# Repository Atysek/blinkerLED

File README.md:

# BlinkerLED
Simple board with few blinking LEDs. The board creates a LED blinking effect, making it perfect for beginners who want to learn the basics of electronics, soldering, and PCB assembly. It is easy to make and can be used as cool decoration for your room.

# PCB & Schematic
The PCB was designed in KiCad.

# BOM – Bill of Materials
| Quantity |	Name |
|----------|-------|
| 1×  | NE555P IC TIMER |
| 1×	| IC SOCKET |
| 10× | LEDs |
| 2×	| Resistors |
| 2×	| Capacitors |
| 1×	| Potentiometer |
| 2×	| Power Connectors |
| 1×	| Custom PCB	Designed in KiCAD |

# REPOSITORIES:
PCB-Pcb design and other files
GERBER-Gerber files for production
PHOTO-Photos

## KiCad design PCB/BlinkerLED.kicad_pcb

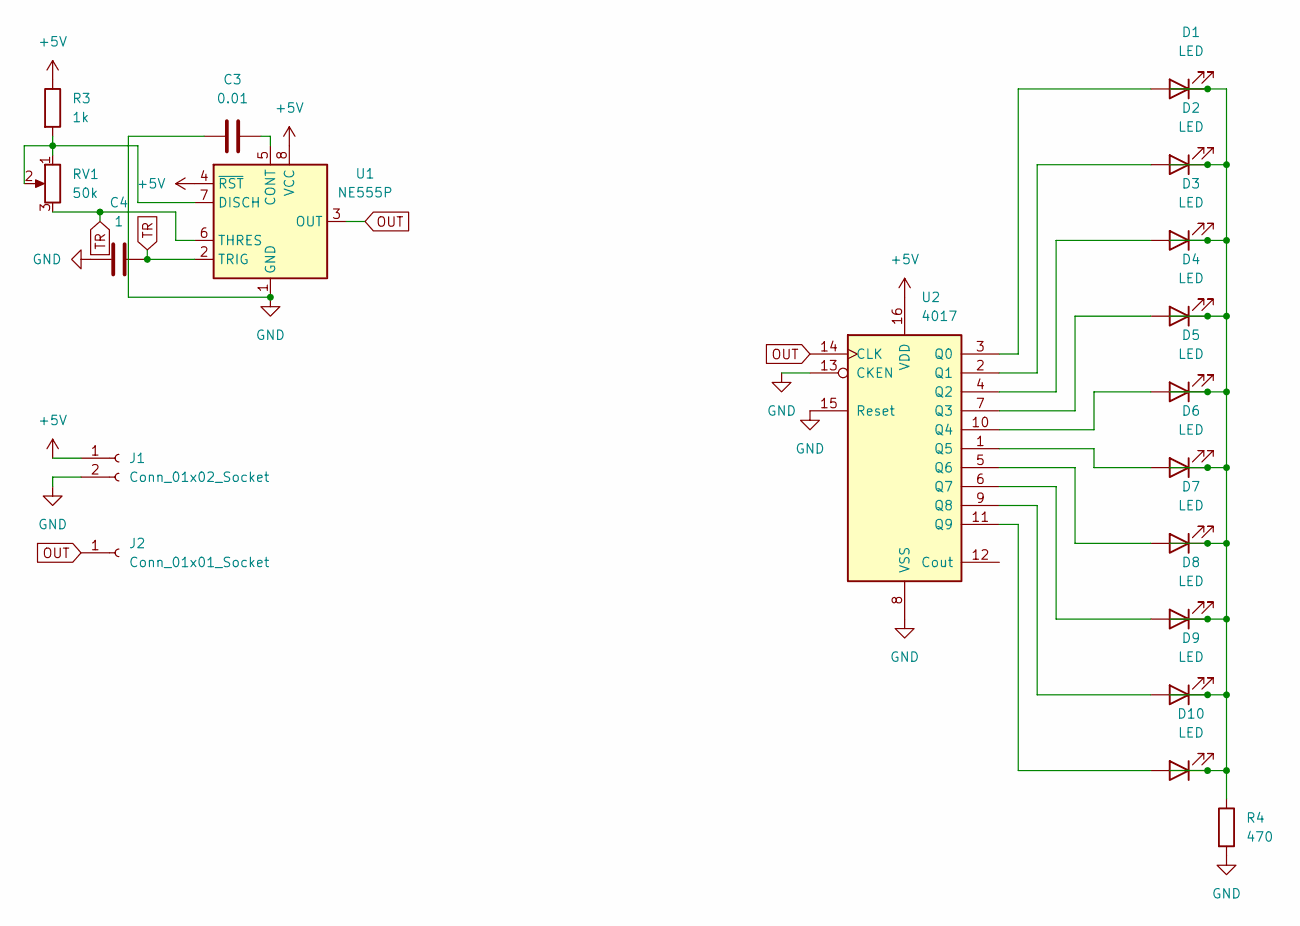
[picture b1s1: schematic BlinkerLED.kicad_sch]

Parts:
C3: 0.01; C_Disc_D7.5mm_W2.5mm_P5.00mm
C4: 1; CP_Radial_D5.0mm_P2.00mm
D1, D2, D3, D4, D5, D6, D7, D8, D9, D10: LED; LED_D3.0mm
J1: Conn_01x02_Socket; PinHeader_1x02_P2.54mm_Vertical
J2: Conn_01x01_Socket; PinHeader_1x01_P2.54mm_Vertical
R3: 1k; R_Axial_DIN0207_L6.3mm_D2.5mm_P7.62mm_Horizontal
R4: 470; R_Axial_DIN0207_L6.3mm_D2.5mm_P7.62mm_Horizontal
RV1: 50k; Potentiometer_Vishay_T93YA_Vertical
U1: NE555P; DIP-8_W7.62mm
U2: 4017; N16

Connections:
+5V: J1.1, R3.1, U1.4 (~RST), U1.8 (VCC), U2.16 (VDD)
GND: C3.1, C4.1, J1.2, R4.2, U1.1 (GND), U2.8 (VSS), U2.13 (CKEN), U2.15 (Reset)
unnamed: D1.2 (A), U2.3 (Q0)
unnamed: D1.1 (K), D2.1 (K), D3.1 (K), D4.1 (K), D5.1 (K), D6.1 (K), D7.1 (K), D8.1 (K), D9.1 (K), D10.1 (K), R4.1
unnamed: D2.2 (A), U2.2 (Q1)
unnamed: D3.2 (A), U2.4 (Q2)
unnamed: D4.2 (A), U2.7 (Q3)
unnamed: D5.2 (A), U2.10 (Q4)
unnamed: D6.2 (A), U2.1 (Q5)
unnamed: D7.2 (A), U2.5 (Q6)
unnamed: D8.2 (A), U2.6 (Q7)
unnamed: D9.2 (A), U2.9 (Q8)
unnamed: D10.2 (A), U2.11 (Q9)
unnamed: C3.2, U1.5 (CONT)
unnamed: R3.2, RV1.1, RV1.2, U1.7 (DISCH)
OUT: J2.1, U1.3 (OUT), U2.14 (CLK)
TR: C4.2, RV1.3, U1.2 (TRIG), U1.6 (THRES)

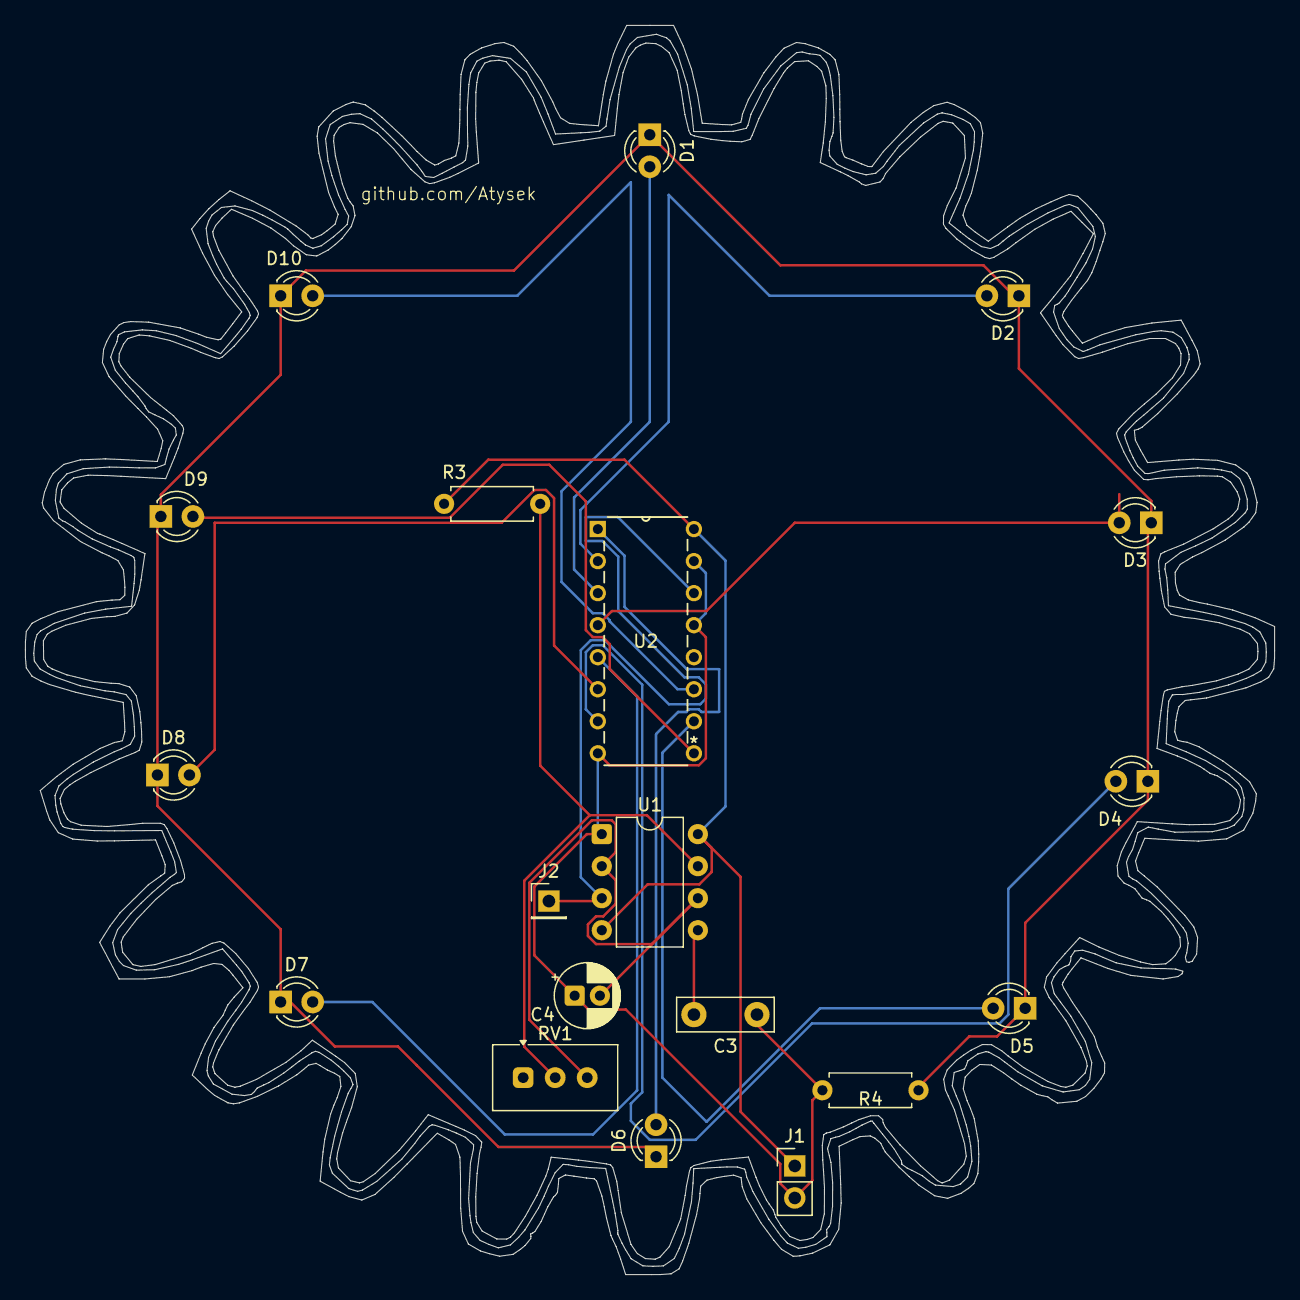
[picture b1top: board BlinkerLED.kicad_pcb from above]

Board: 2 copper layers, 99.1 x 99.1 mm, 19 parts (0 on the bottom side), 17 nets.

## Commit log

2026-02-10 Rename BlinkerLED.png to PHOTOS/BlinkerLED.png
